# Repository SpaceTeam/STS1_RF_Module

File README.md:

# STS1 RF Module

This PCB is the RF subsystem of the STS1 COBC ("Communication and On Board Computer") isolated on a separate PCB to test the RF subsystem.  
The complete RF path was simulated using QUCS (see [the STS1_RF_Simulations repo](https://github.com/SpaceTeam/STS1_RF_Simulations) for the files).

It is based around the Si4463 RF IC and features an LNA, 2W power amplifier and filtering built for our CubeSat and is designed for a frequency around 435MHz.

Feel free to use this for whatever you want but there are two important things to consider:
- 2W is way more than legal without some form of license in most countries so make sure that whatever you are planning to do is legal in your country.
- The filtering and matching is designed for 435MHz. For any other frequency you'll probably go into the QUCS project and find suitable values for your frequency.
  - The matching of the Si4463 is described in [AN643](https://www.silabs.com/documents/public/application-notes/AN643.pdf) and [AN648](https://www.silabs.com/documents/public/application-notes/AN648.pdf)
  - The matching of the PA and LNA is done using the [QUCS matching network calculation tool](https://qucs-help.readthedocs.io/en/0.0.19/matching.html)
  - The low pass filters most likely can stay the same if you don't drastically change the frequency
  - The band pass filters are stolen from [ORESAT0 C3](https://github.com/oresat/oresat-c3/) so you'll have to figure this out on your own :P
- When using this in space, you'll want to add some form of watchdog to the `TX_Block` input and latch-up protection for at least the 3.3V rail (the power amplifier has it's own e-fuse on the 5V rail)

## Current state

### v1.0

Currently untested!  
The TX path excluding the RF switch were mostly tested before but the rest is untested.

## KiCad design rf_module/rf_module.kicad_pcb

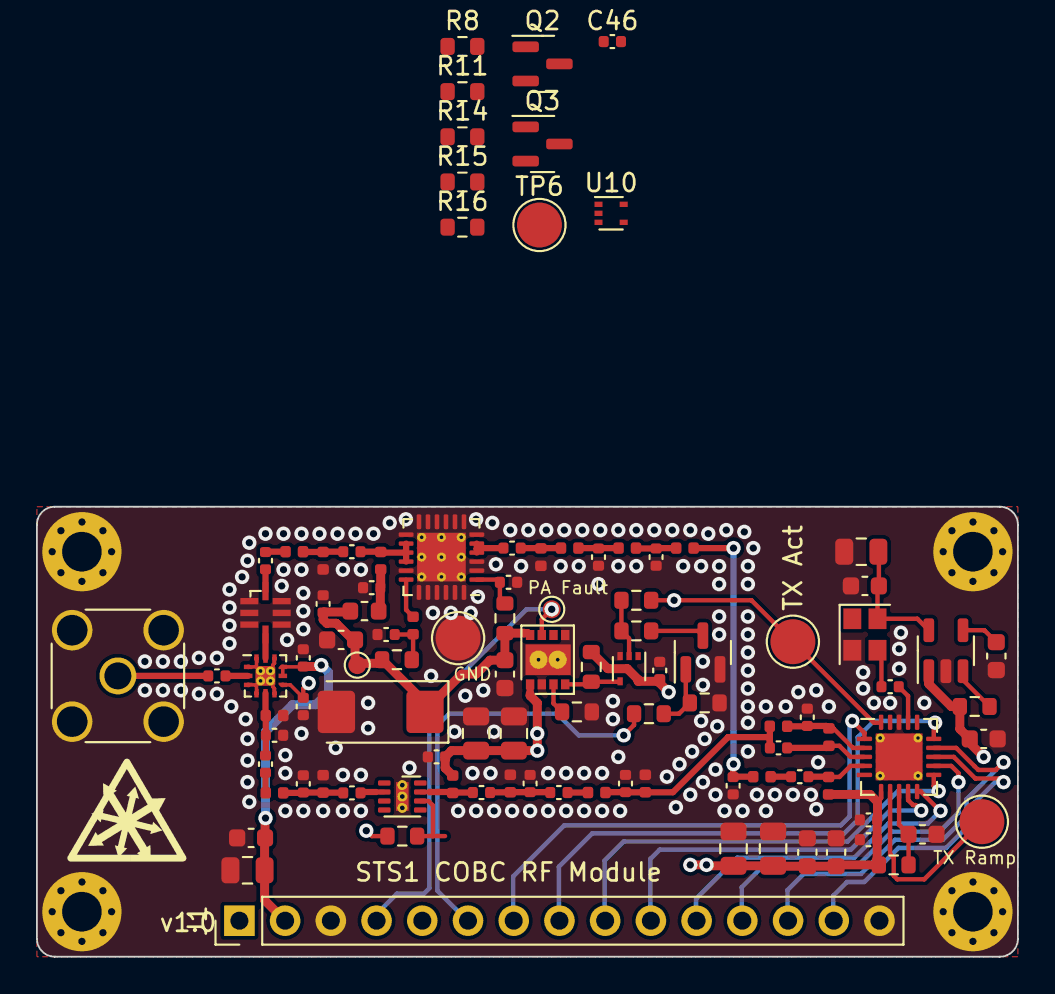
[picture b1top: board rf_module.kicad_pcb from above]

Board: 4 copper layers, 54.5 x 25.0 mm, 107 parts (0 on the bottom side), 63 nets.

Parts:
C1, C6, C15, C23, C33, C39: 100n; C_0603_1608Metric
C2, C4: 7.5p; C_0402_1005Metric
C3, C21: 10n; C_0603_1608Metric
C5, C25: 4.7µ; C_0805_2012Metric
C7, C11, C24, C29, C44: 24p; C_0402_1005Metric
C8, C9, C12, C14, C18, C19, C30, C31, C32, C36, C42, C43, C46: 100p; C_0402_1005Metric
C10, C28: 2p; C_0402_1005Metric
C13: 1u; C_0805_2012Metric
C16: 33p; C_0402_1005Metric
C17: 9.1p; C_0402_1005Metric
C20: 4.7p; C_0402_1005Metric
C22: 2.2p; C_0402_1005Metric
C26: 15p; C_0402_1005Metric
C27: 47µ; C_0805_2012Metric
C34: 1µ; C_0805_2012Metric
C35: 100n; C_0402_1005Metric
C37: 50p; C_0402_1005Metric
C38: 10u; C_0805_2012Metric
C40: 10u; CP_EIA-6032-28_Kemet-C
C41: 1n; C_0603_1608Metric
C45: 3.3p; C_0402_1005Metric
FB1: Ferrite_Bead; L_0603_1608Metric
H1, H2, H3, H4: MH; MountingHole_2.2mm_M2_Pad_Via
J1: Conn_01x15; PinHeader_1x15_P2.54mm_Vertical
J2: UHF; SMA_Amphenol_132134_Vertical
L1, L3, L12: 33n; L_0402_1005Metric
L2: 51n; L_0402_1005Metric
L4, L6, L11, L14: 5.6n; L_0402_1005Metric
L5, L7, L13, L15: 68n; L_0402_1005Metric
L8: 220n; L_0402_1005Metric
L9: 62n; L_0402_1005Metric
L10: 56n; L_0402_1005Metric
L16: 4n; L_0402_1005Metric
L17: 18n; L_0402_1005Metric
L18: 8.2n; L_0402_1005Metric
L19: 47n; L_0402_1005Metric
Q1, Q2, Q3: SQ2318; SOT-23
R1, R12: 100k; R_0603_1608Metric
R2, R5, R8, R11, R16: 100; R_0603_1608Metric
R3, R4, R14, R15: 10k; R_0603_1608Metric
R6: 4.7; R_0603_1608Metric
R7: 33k; R_0603_1608Metric
R9: 240; R_0603_1608Metric
R10: 280; R_0603_1608Metric
R13: 110k; R_0603_1608Metric
TP1: TXRAMP; TestPoint_Pad_D2.5mm
TP2: TX_Active; TestPoint_Pad_D2.5mm
TP3: GND; TestPoint_Pad_D2.5mm
TP4: PA_Fault; TestPoint_Pad_D1.0mm
TP5: 5V_PA; TestPoint_Pad_D1.0mm
TP6: RX_Active; TestPoint_Pad_D2.5mm
U1: LP2985-1.8; SOT-23-5
U2: TYKTBCSANF-26.000000; Crystal_SMD_2520-4Pin_2.5x2.0mm
U3, U10: NL17SV04XV5T2G; SOT-553
U4: Si4463; QFN-20-1EP_4x4mm_P0.5mm_EP2.6x2.6mm_ThermalVias
U5: TQP3M9036; DFN-8-1EP_2x2mm_P0.5mm_EP0.7x1.6mm_ThermalVias
U6: LFCG-490+; GE0805C-2
U7: F2972; IDT_NEG-12-1EP_2x2mm_P0.5mm_EP1.1x1.1mm_ThermalVias
U8: FPF2701; MLP-8
U9: TQP7M9106; QFN-24-1EP_4x4mm_P0.5mm_EP2.7x2.7mm_ThermalVias

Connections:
+3V3: C1.1, C8.2, C16.1, C19.1, C21.1, C23.1, C25.1, C27.1, C31.1, C33.1, C34.1, C46.1, J1.2, L8.2, R1.1, R6.2, R12.2, U1.1 (VIN), U3.5 (VCC), U4.6 (VDD), U7.8 (EN), U7.9 (VCC), U10.5 (VCC)
+5V: C13.1, C14.1, C38.1, J1.1, L7.2, U8.1 (VIN)
/3V3_Si_Filt: C15.1, R6.1, U4.8 (VDD)
/PA_Block: J1.6, R2.1
/PA_Enable: J1.5, R16.1
/PA_Fault: J1.4, TP4.1, U8.7 (FLAGB)
/RF_BPF1_Mid: C28.1, L13.2
/RF_BPF1_Out: C18.2, C24.1, L11.2, L13.1
/RF_BPF2_In: C10.2, C11.1, C12.1, L6.2
/RF_BPF2_Mid: C10.1, L5.2
/RF_BPF2_Out: C7.1, C22.2, L4.2, L5.1, L10.2
/RF_Connector: C32.2, J2.1 (In)
/RF_LNA_In: C18.1, U5.2 (RFIN)
/RF_LNA_Out: C12.2, L7.1, U5.7 (RFOUT)
/RF_LPF1_In: C26.1, L1.1, L12.2
/RF_LPF1_Mid1: C2.1, L1.2, L2.1
/RF_LPF1_Mid2: C4.1, L2.2, L3.1
/RF_LPF1_Out: C37.1, L3.2, L16.2
/RF_LPF2_In: C45.2, U6.8 (IN)
/RF_Si_Inn: C22.1, L9.2, U4.3 (RXn)
/RF_Si_Inp: C20.1, L9.1, L10.1, U4.2 (RXp)
/RF_Si_Match: C17.2, L12.1
/RF_Si_Out: C17.1, L8.1, U4.4 (TX)
/RF_Sw: C32.1, U7.2 (RFC)
/RF_Sw1: C28.2, C29.1, L14.2, U7.5 (RF1)
/RF_Sw2: U6.4 (OUT), U7.11 (RF2)
/RX_Active: TP6.1, U4.19 (GPIO2), U10.2
/Si4463_GPIO0: J1.10, U4.9 (GPIO0)
/Si4463_GPIO1: J1.11, U4.10 (GPIO1)
/Si4463_SDI: J1.13, U4.14 (SDI)
/Si4463_SDN: J1.7, U4.1 (SDN)
/Si4463_SDO: J1.14, U4.13 (SDO)
/Si4463_SPI_CLK: J1.12, U4.12 (SCLK)
/Si4463_nIRQ: J1.9, U4.11 (~IRQ)
/Si4463_nSEL: J1.8, U4.15 (~SEL)
/TX_Active: C30.1, R4.1, TP2.1, U4.20 (GPIO3), U7.7 (Vctl)
/UHF_PA/5V_TX_Filt: C43.2, FB1.1, L17.1
/UHF_PA/5V_TX_U: C39.1, C40.1, C41.1, C42.1, FB1.2, R9.1, R10.2, TP5.1, U8.8 (VOUT)
/UHF_PA/RF_Amp_In: C37.2, U9.4 (RFIN), U9.5 (RFIN)
/UHF_PA/RF_Amp_Match1: C44.2, L18.1, L19.1
/UHF_PA/RF_Amp_Match2: C45.1, L19.2
/UHF_PA/RF_Amp_Out: C44.1, L17.2, U9.14 (RFOUT/VCC), U9.15 (RFOUT/VCC), U9.16 (RFOUT/VCC)
/UHF_PA/~PA_EN: R12.1, U3.4, U8.4 (ON)
GND: C1.2, C2.2, C3.2, C4.2, C5.2, C6.2, C7.2, C8.1, C11.2, C13.2, C14.2, C15.2, C16.2, C19.2, C20.2, C21.2, C23.2, C24.2, C25.2, C26.2, C27.2, C29.2, C30.2, C31.2, C33.2, C34.2, C35.2, C36.2, C38.2, C39.2, C40.2, C41.2, C42.2, C43.1, C46.2, H1.1, H2.1, H3.1, H4.1, J1.3, J1.15, J2.2 (Ext), L4.1, L6.1, L11.1, L14.1, L16.1, L18.2, Q1.2 (S), Q2.2 (S), Q3.2 (S), R3.1, R13.2, R14.1, R15.1, TP3.1, U1.2 (GND), U2.2 (GND), U3.3 (GND), U4.18 (GND), U4.21 (GND), U5.9 (GND), U6.1 (GND), U6.2 (GND), U6.3 (GND), U6.5 (GND), U6.6 (GND), U6.7 (GND), U7.1 (GND), U7.3 (GND), U7.4 (GND), U7.6 (GND), U7.10 (GND), U7.12 (GND), U7.13 (GND), U8.2 (PGOOD), U8.5 (GND), U8.9 (GND), U9.2 (GND), U9.3 (GND), U9.6 (GND), U9.7 (GND), U9.8 (GND), U9.9 (GND), U9.10 (GND), U9.11 (GND), U9.12 (GND), U9.13 (GND), U9.17 (GND), U9.19 (GND), U9.20 (GND), U9.21 (GND), U9.22 (GND), U9.23 (GND), U9.24 (GND), U9.25 (EP), U10.3 (GND)
unnamed: C35.1, L15.2, R9.2
unnamed: Q1.3 (D), R5.1
unnamed: Q1.1 (G), R2.2, R3.2
unnamed: Q2.3 (D), R8.1
unnamed: Q2.1 (G), R11.2, R14.2
unnamed: Q3.3 (D), R11.1
unnamed: Q3.1 (G), R15.2, R16.2
unnamed: R4.2, R5.2, R8.2, U3.2
unnamed: R7.2, U10.4
unnamed: C3.1, U1.4 (BP)
unnamed: R1.2, U1.3 (ON/~OFF)
unnamed: C5.1, C6.1, U1.5 (VOUT), U2.4 (VDD)
unnamed: C9.1, U2.3 (OUT)
unnamed: TP1.1, U4.7 (TXRAMP)
unnamed: C9.2, U4.17 (XIN)
unnamed: R7.1, U5.6 (Shut_Down)
unnamed: R13.1, U8.3 (ISET)
unnamed: L15.1, U9.18 (IREF)
unnamed: C36.1, R10.1, U9.1 (VBIAS)

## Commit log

2023-03-02 feat: Schematic done
2023-03-03 feat: minor schematic adjustments and pcb layout
2023-03-03 feat: colour RF netclass purple
2023-03-03 fix: DRC
2023-03-03 feat: add readme and license
2023-03-03 feat: add current status of v1.0 to readme
2023-03-03 fix: typo in readme
2023-05-24 feat: implement LNA activation on RX and PA_Enable in schematic (layout TODO)
2023-07-08 fix: component values of TX PA input matching and filter
